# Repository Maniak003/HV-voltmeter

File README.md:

<!DOCTYPE html>
<html lang="en" data-color-mode="auto" data-light-theme="light" data-dark-theme="dark">
  <head>
    <meta charset="utf-8">
  </head>
    <body class="logged-in env-production page-responsive page-blob" style="word-wrap: break-word;">
      <p> Hight voltage (3kV) voltrmeter. </p>
      
    </body>
</html>

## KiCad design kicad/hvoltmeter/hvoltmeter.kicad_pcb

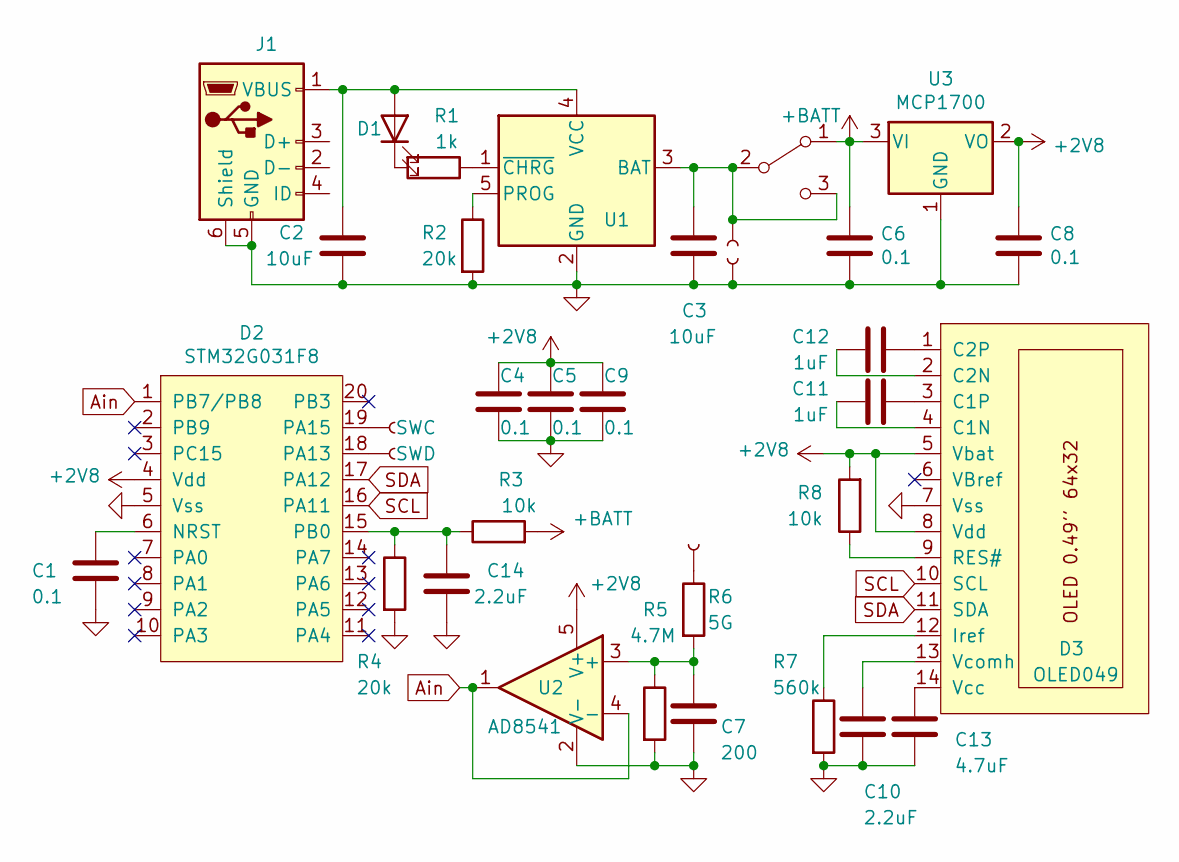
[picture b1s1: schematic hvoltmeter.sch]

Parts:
C1, C4, C5, C6, C8: 0.1; C_0603_1608Metric
C2, C3: 10uF; C_0603_1608Metric
C7: 200; C_0603_1608Metric
C9: 0.1; C_0402_1005Metric
C10, C14: 2.2uF; C_0402_1005Metric
C11, C12: 1uF; C_0402_1005Metric
C13: 4.7uF; C_0402_1005Metric
D1: LED; LED_0603_1608Metric
D2: STM32G031F8; TSSOP-20_4.4x6.5mm_P0.65mm
D3: OLED049
J1: USB_B_Micro-Connector; USB_Micro-B_Molex_47346-0001
J2: SWC; SMD-CONN
J3: SWD; SMD-CONN
J4, J5, J6: Conn; SMD-CONN
R1: 1k; R_0603_1608Metric
R2, R4: 20k; R_0402_1005Metric
R3, R8: 10k; R_0402_1005Metric
R5: 4.7M; R_0603_1608Metric
R6: 5G; R_2512_6332Metric
R7: 560k; R_0402_1005Metric
SW1: SW_DPDT_x2; MySwithc
U1: LTC4054ES5-4.2; TSOT-23-5
U2: AD8541; TSOT-23-5
U3: MCP1700; SOT-23

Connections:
+2V8: C4.1, C5.1, C8.1, C9.1, D2.4 (Vdd), D3.5 (Vbat), D3.8 (Vdd), R8.2, U2.5 (V+), U3.2 (VO)
+BATT: C6.1, R3.2, SW1.1 (A), U3.3 (VI)
Ain: D2.1 (PB7/PB8), U2.1, U2.4 (-)
GND: C1.2, C2.2, C3.2, C4.2, C5.2, C6.2, C7.2, C8.2, C9.2, C10.1, C13.1, C14.1, D2.5 (Vss), D3.7 (Vss), J1.5 (GND), J1.6 (Shield), J5.1, R2.2, R4.2, R5.2, R7.2, U1.2 (GND), U2.2 (V-), U3.1 (GND)
unnamed: C1.1, D2.6 (NRST)
unnamed: C2.1, D1.2 (A), J1.1 (VBUS), U1.4 (VCC)
unnamed: C3.1, J4.1, SW1.2 (B), SW1.3 (C), U1.3 (BAT)
unnamed: C7.1, R5.1, R6.2, U2.3 (+)
unnamed: C10.2, D3.13 (Vcomh)
unnamed: C11.1, D3.1 (C2P)
unnamed: C11.2, D3.2 (C2N)
unnamed: C12.1, D3.3 (C1P)
unnamed: C12.2, D3.4 (C1N)
unnamed: C13.2, D3.14 (Vcc)
unnamed: C14.2, D2.15 (PB0), R3.1, R4.1
unnamed: D1.1 (K), R1.2
unnamed: D2.18 (PA13), J3.1
unnamed: D2.19 (PA15), J2.1
unnamed: D3.9 (RES#), R8.1
unnamed: D3.12 (Iref), R7.1
unnamed: J6.1, R6.1
unnamed: R1.1, U1.1 (~CHRG)
unnamed: R2.1, U1.5 (PROG)
SCL: D2.16 (PA11), D3.10 (SCL)
SDA: D2.17 (PA12), D3.11 (SDA)

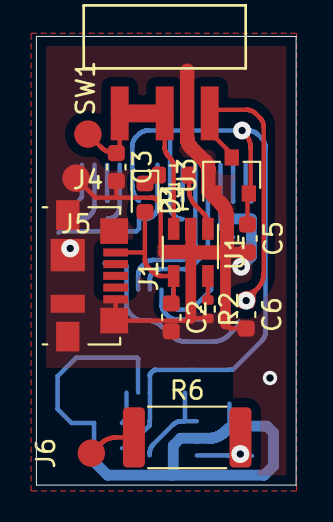
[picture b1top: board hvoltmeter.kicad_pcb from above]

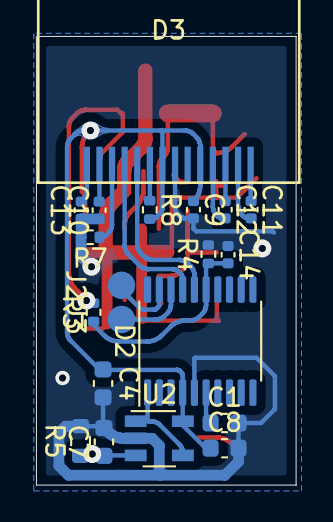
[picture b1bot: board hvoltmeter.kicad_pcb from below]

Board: 2 copper layers, 14.4 x 24.9 mm, 35 parts (20 on the bottom side), 25 nets.

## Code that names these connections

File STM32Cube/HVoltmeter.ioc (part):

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PA11\ [PA9].Mode=I2C
Mcu.UserName=STM32G031F8Px
PA12\ [PA10].Mode=I2C
PB0.GPIO_Label=Batt
RCC.SYSCLKSource=RCC_SYSCLKSOURCE_PLLCLK
PB7.GPIOParameters=GPIO_Label
PA12\ [PA10].Signal=I2C2_SDA
RCC.HSE_VALUE=8000000
PB0.Mode=IN8
board=custom
PB0.GPIOParameters=GPIO_Label
PB7.Signal=ADC1_IN11
PA11\ [PA9].Signal=I2C2_SCL
Mcu.Name=STM32G031F(4-6-8)Px
PB7.GPIO_Label=AIn
RCC.SYSCLKFreq_VALUE=64000000
Mcu.Package=TSSOP20
PB7.Mode=IN11
PB0.Signal=ADC1_IN8

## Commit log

2022-09-23 новый файл: Documents/ER-OLED0.49-1_Series_Datasheet.pdf новый файл: STM32Cube/HV/.cproject новый файл: STM32Cube/HV/.mxproject новый файл: STM32Cube/HV/.project новый файл: STM32Cube/HV/.settings/la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
2022-09-25 удалено: STM32Cube/HV/.cproject удалено: STM32Cube/HV/.mxproject удалено: STM32Cube/HV/.project удалено: STM32Cube/HV/.settings/language.settings.xml удалено: STM32Cube/HV/.settings/stm32cubeide.proj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
2022-09-25 новый файл: STM32Cube/.cproject новый файл: STM32Cube/.mxproject новый файл: STM32Cube/.project новый файл: STM32Cube/.settings/language.settings.xml новый файл: STM32Cube/.settings/stm32cubeide.proj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
2022-09-25 изменено: STM32Cube/.cproject новый файл: STM32Cube/Release/Core/Src/main.d новый файл: STM32Cube/Release/Core/Src/main.o новый файл: STM32Cube/Release/Core/Src/main.su новый файл: STM32Cube/Release/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
2022-09-25 новый файл: kicad/hvoltmeter/hvoltmeter-rescue.dcm новый файл: kicad/hvoltmeter/hvoltmeter-rescue.lib новый файл: kicad/hvoltmeter/sym-lib-table
2022-09-26 изменено: kicad/hvoltmeter/hvoltmeter.kicad_pcb изменено: kicad/hvoltmeter/hvoltmeter.kicad_pcb-bak изменено: kicad/hvoltmeter/hvoltmeter.sch изменено: kicad/hvoltmeter/hvoltmeter.sch-bak
2022-09-26 изменено: STM32Cube/.cproject изменено: STM32Cube/.mxproject изменено: STM32Cube/.project изменено: STM32Cube/.settings/language.settings.xml изменено: STM32Cube/Core/Inc/main.h изменено: STM32Cube/C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
2022-09-26 изменено: STM32Cube/.cproject новый файл: STM32Cube/Release/HVoltmeter.hex изменено: STM32Cube/Release/makefile
2022-09-29 изменено: kicad/hvoltmeter/hvoltmeter.kicad_pcb изменено: kicad/hvoltmeter/hvoltmeter.kicad_pcb-bak
2022-09-30 новый файл: Documents/hvoltmeter.png изменено: kicad/hvoltmeter/hvoltmeter.pro изменено: kicad/hvoltmeter/hvoltmeter.sch изменено: kicad/hvoltmeter/hvoltmeter.sch-bak
2022-10-01 изменено: STM32Cube/.settings/language.settings.xml изменено: STM32Cube/Core/Src/stm32g0xx_it.c изменено: STM32Cube/Release/Core/Src/stm32g0xx_it.o удалено: STM32Cube/Release/HVoltmeter.bin удалено: 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
2022-10-20 новый файл: Documents/IMG_20221002_154138.jpg изменено: STM32Cube/.settings/language.settings.xml
2022-10-20 изменено: README.md
